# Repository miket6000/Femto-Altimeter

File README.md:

Femto-Altimeter
================
The Femto-Altimeter is my attempt to create the smallest possible altimeter for model rocketry with the following features:
- Bluetooth LE connection to a phone to arm, check continuity and configure.
- Capable of electronic deployment.
- Altitude logging.
- Run off a single cell lithium battery, with external capacitor for deployment (if necessary).
- Be as small as possible while avoiding High Density Interconnect (uvia, etc) to allow lower cost construction.
- Designed to use parts avaialble in stock at JLCPCB at the time of design.

The resulting Femto is approximately 10x18mm (smaller than 1/2"x3/4") excluding battery. Weight will be determined when first samples arrive, but it's expected to be less than 2g.

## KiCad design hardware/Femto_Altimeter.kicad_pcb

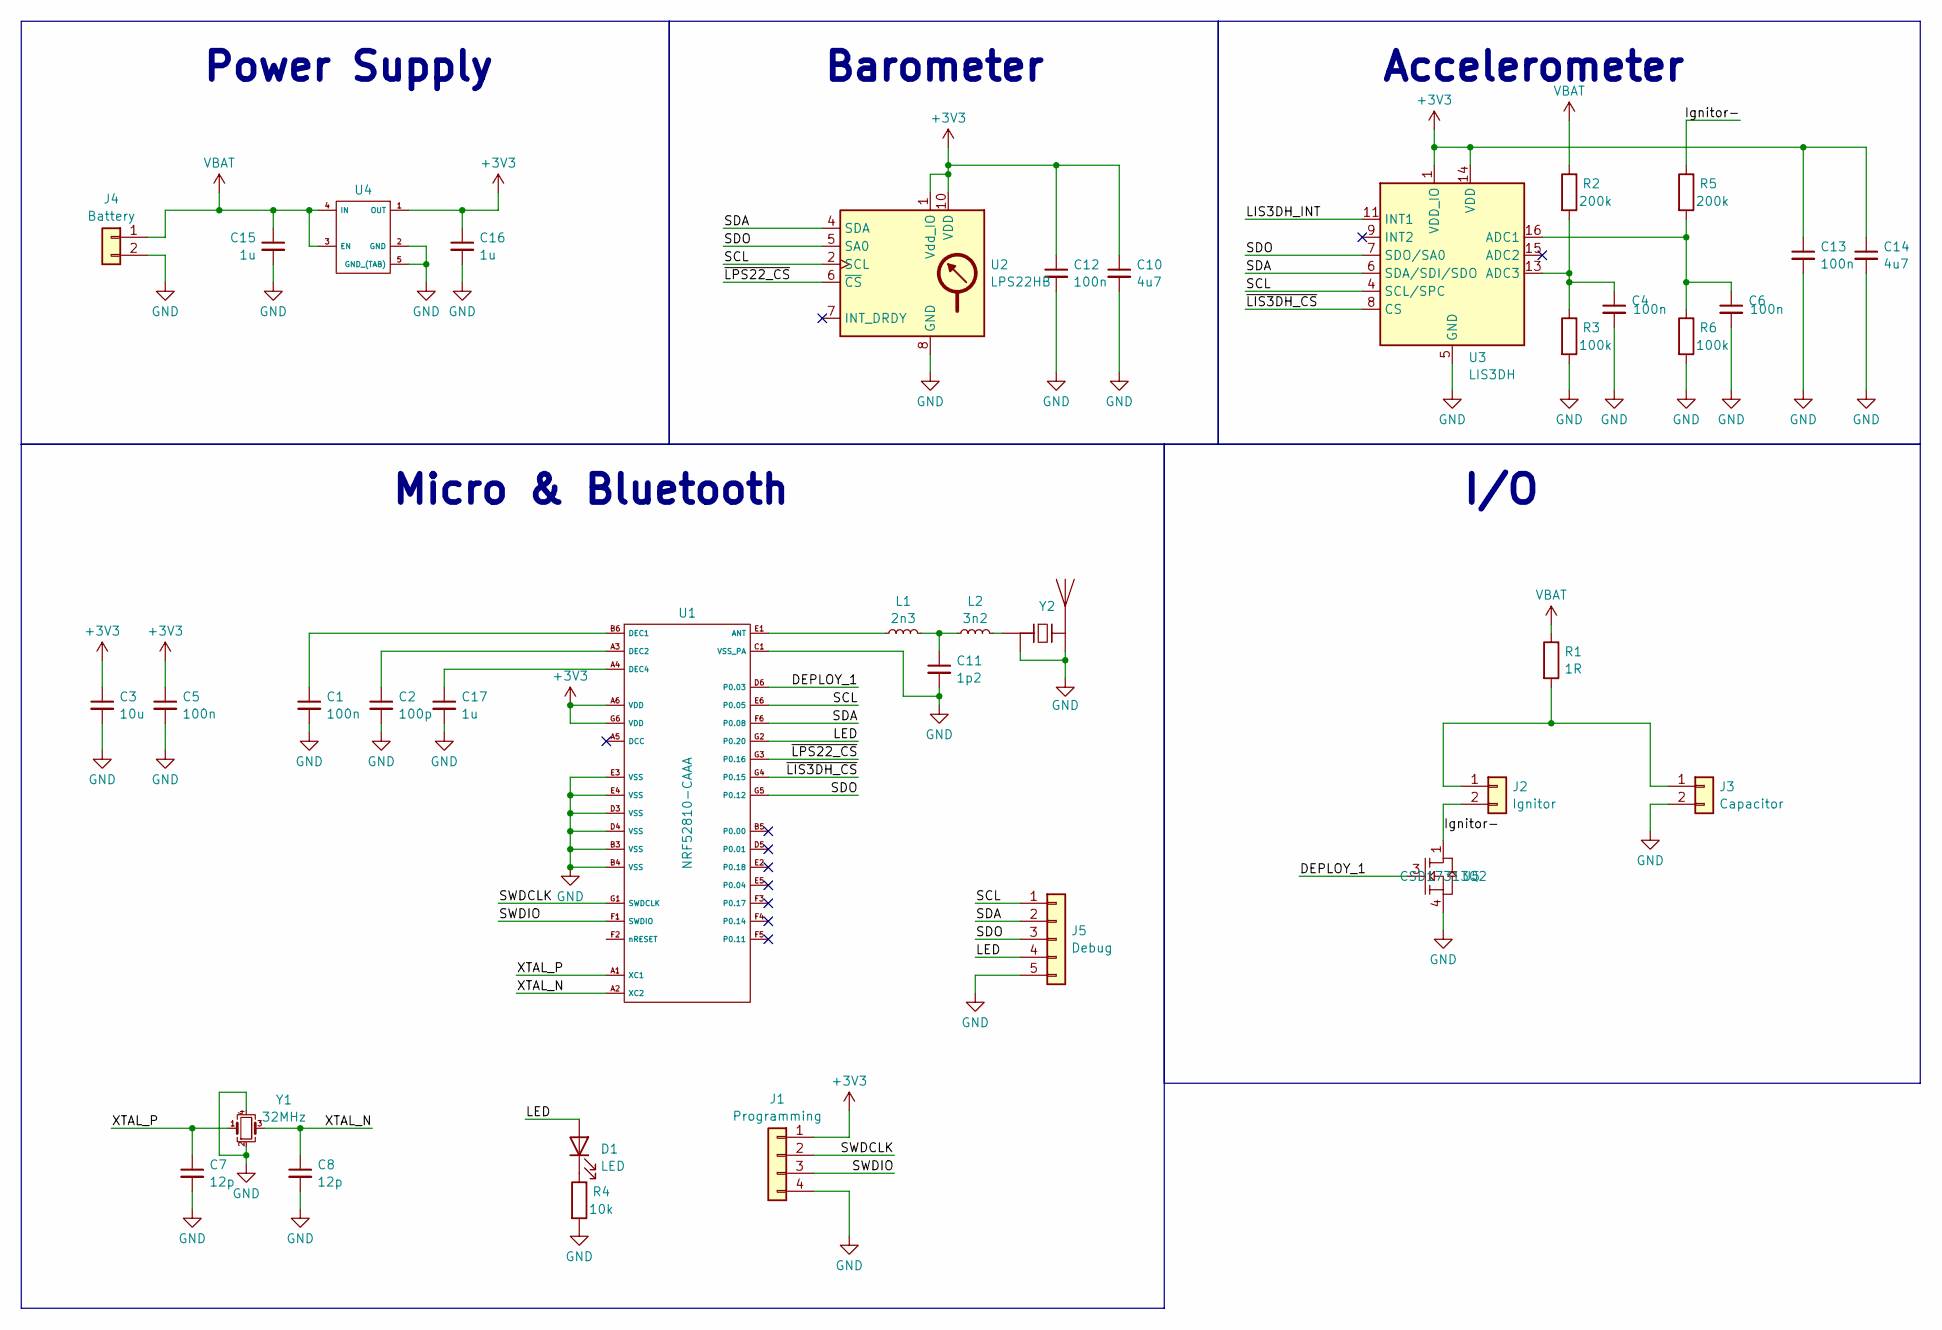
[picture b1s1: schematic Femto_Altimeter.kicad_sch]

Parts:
C1, C4, C5, C6, C12, C13: 100n; C_0201_0603Metric
C2: 100p; C_0201_0603Metric
C3: 10u; C_0603_1608Metric
C7, C8: 12p; C_0201_0603Metric
C10, C14: 4u7; C_0402_1005Metric
C11: 1p2; C_0201_0603Metric; JLC Part Number C1855072
C15, C16, C17: 1u; C_0201_0603Metric
D1: LED; LED_0402_1005Metric
J1: Programming; Edge_Pads_1x4_P1.0
J2: Ignitor; Edge_Pads_1x2_P1.5
J3: Capacitor; Edge_Pads_1x2_P1.5
J4: Battery; Edge_Pads_1x2_P1.5
J5: Debug; Edge_Pads_1x5_P1.0
L1: 2n3; L_0201_0603Metric; JLC Part Number C2048374
L2: 3n2; L_0201_0603Metric; JLC Part Number C408626
R1: 1R; R_0805_2012Metric
R2, R5: 200k; R_0201_0603Metric
R3, R6: 100k; R_0201_0603Metric
R4: 10k; R_0201_0603Metric
U1: NRF52810-CAAA; WLCSP-33_2.486x2.464mm; JLC Part Number C3606661
U2: LPS22HB; ST_HLGA-10_2x2mm_P0.5mm_LayoutBorder3x2y; JLC Part Number C94049
U3: LIS3DH; LGA-16_3x3mm_P0.5mm_LayoutBorder3x5y; JLC Part Number C15134
U4: OnSemi_XDFN4-1EP_1.0x1.0mm_EP0.52x0.52mm; JLC Part Number C892227
U5: CSD17313Q2; Texas_DQK; JLC Part Number C2862001
Y1: 32MHz; Crystal_SMD_2520-4Pin_2.5x2.0mm; JLC Part Number C2149238
Y2: Antenna_Chip_Pulse_Larsen_W3008; JLC Part Number C581402

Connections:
+3V3: C3.1, C5.1, C10.1, C12.1, C13.1, C14.1, C16.1, J1.1, U1.A6 (VDD), U1.G6 (VDD), U2.1 (Vdd_IO), U2.10 (VDD), U3.1 (VDD_IO), U3.14 (VDD), U4.1 (OUT)
/DEPLOY_1: U1.D6 (P0.03), U5.3 (G)
/Ignitor-: J2.2, R5.1, U5.1 (D), U5.2 (D), U5.5 (D), U5.6 (D), U5.8 (D)
/LED: D1.2 (A), J5.4, U1.G2 (P0.20)
/LIS3DH_INT: U3.11 (INT1)
/SCL: J5.1, U1.E6 (P0.05), U2.2 (SCL), U3.4 (SCL/SPC)
/SDA: J5.2, U1.F6 (P0.08), U2.4 (SDA), U3.6 (SDA/SDI/SDO)
/SDO: J5.3, U1.G5 (P0.12), U2.5 (SA0), U3.7 (SDO/SA0)
/SWDCLK: J1.2, U1.G1 (SWDCLK)
/SWDIO: J1.3, U1.F1 (SWDIO)
/XTAL_N: C8.1, U1.A2 (XC2), Y1.3
/XTAL_P: C7.1, U1.A1 (XC1), Y1.1
/~LIS3DH_CS: U1.G4 (P0.15), U3.8 (CS)
/~LPS22_CS: U1.G3 (P0.16), U2.6 (~CS)
GND: C1.2, C2.2, C3.2, C4.2, C5.2, C6.2, C7.2, C8.2, C10.2, C11.2, C12.2, C13.2, C14.2, C15.2, C16.2, C17.2, J1.4, J3.2, J4.2, J5.5, R3.2, R4.2, R6.2, U1.B3 (VSS), U1.B4 (VSS), U1.C1 (VSS_PA), U1.D3 (VSS), U1.D4 (VSS), U1.E3 (VSS), U1.E4 (VSS), U2.3 (GND), U2.8 (GND), U2.9 (GND), U3.5 (GND), U3.10 (GND), U3.12 (GND), U4.2 (GND), U4.5 (GND_(TAB)), U5.4 (S), U5.7 (S), Y1.2, Y1.4, Y2.2 (GND), Y2.3 (GND)
unnamed: C11.1, L1.1, L2.2
unnamed: D1.1 (K), R4.1
unnamed: J2.1, J3.1, R1.2
unnamed: L1.2, U1.E1 (ANT)
unnamed: C1.1, U1.B6 (DEC1)
unnamed: C2.1, U1.A3 (DEC2)
unnamed: C17.1, U1.A4 (DEC4)
unnamed: C6.1, R5.2, R6.1, U3.16 (ADC1)
unnamed: C4.1, R2.2, R3.1, U3.13 (ADC3)
unnamed: L2.1, Y2.1 (Feed)
VBAT: C15.1, J4.1, R1.1, R2.1, U4.3 (EN), U4.4 (IN)

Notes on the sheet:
Micro & Bluetooth
Barometer
I/O
Power Supply
Accelerometer

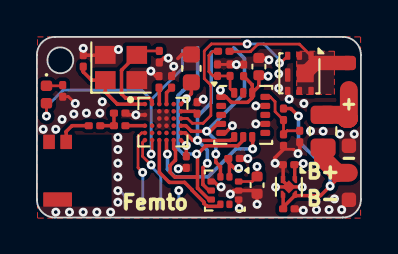
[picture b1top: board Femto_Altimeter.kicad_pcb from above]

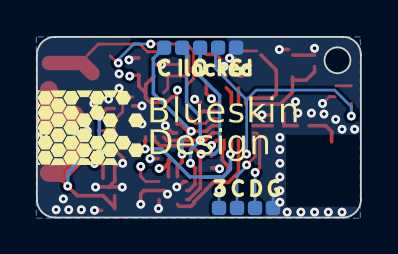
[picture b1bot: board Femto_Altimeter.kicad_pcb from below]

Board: 4 copper layers, 18.0 x 10.0 mm, 37 parts (2 on the bottom side), 25 nets.

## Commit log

2024-03-17 Added front render
2024-03-17 Create README.md
    Initial Readme
2024-03-17 Update README.md
    Added render and additional design constraints
2024-03-17 Adding schematic
